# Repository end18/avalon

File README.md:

Avalon Gen3 Hasher
------------------

This project contains a circuit board, firmware and cgminer/bfgminer patch to get the new Avalon Gen3 ASICs (A3233Q48) hashing.

**Board features:**

  - Very efficient (~90%) DC/DC converter to power the ASICs
  - Adjustable voltage (0.75 - 1.25 V) to choose between efficiency and overclocking
  - USB-Interface to connect to a host running cgminer or bfgminer
  - TWI interface to chain multiple boards together
  - 100% flat surface on the bottom side to mount a usual heatsink
  - On-board temperature management
  - Fan connector with rotation speed measurement and PWM-control
  - Indicator LED to report USB-activity
  - 4-layer PCB for optimal heat/current transportation

**cgminer/bfgminer patch features:**

  - Reporting temperature, real ASIC frequency and fan-speed back to the host
  - Control of ASIC frequency in a big range from 62.5 to 5000 MHz in smallest possible steps
  - Control of a desired temperature

**Get support:**

* [Forum thread]
* - Will be updated soon.

**Get a board:**

Someone is selling some boards in the [Forum thread] soon.

  [Forum thread]: comming soon.

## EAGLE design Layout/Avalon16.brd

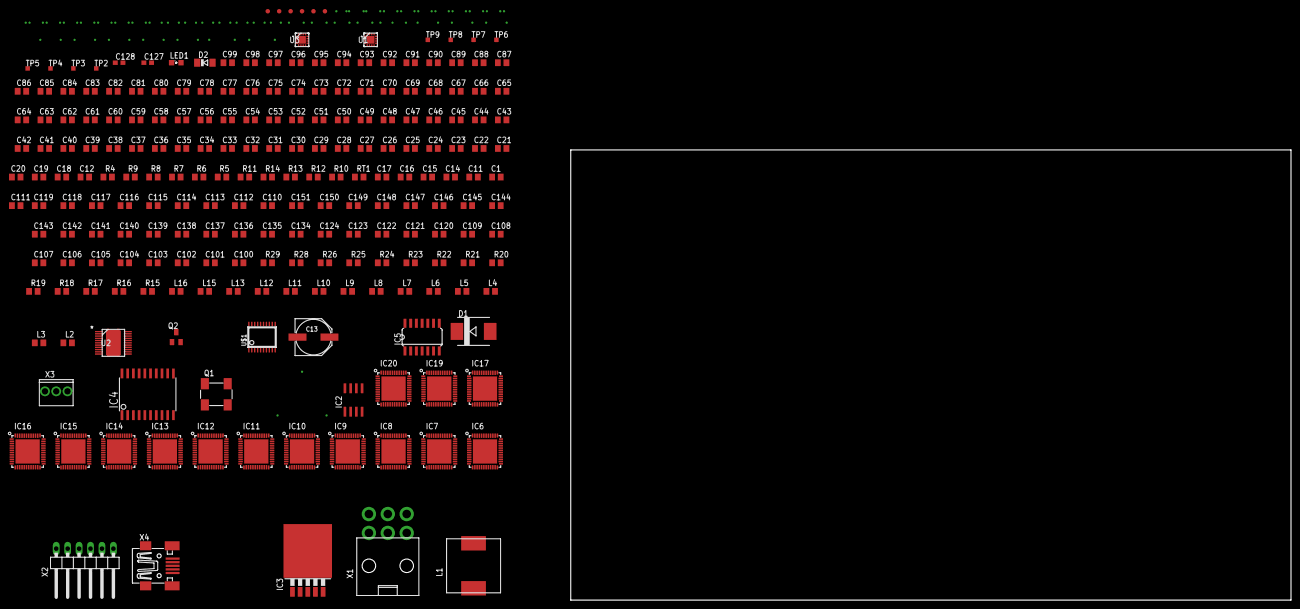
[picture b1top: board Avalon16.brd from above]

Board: 2 copper layers, 160.0 x 100.0 mm, 264 parts (0 on the bottom side), 115 nets, no tracks yet.

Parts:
C1, C11, C14, C15, C16: 100n; C0805
C12, C18, C19, C20, C21, C22, C23, C24, C25, C26, C27, C28, C29, C30, C31, C32, C33, C34, C35, C36, C37, C38, C39, C40, C41, C42, C43, C44, C45, C46, C47, C48, C49, C50, C51, C52, C53, C54, C55, C56, C57, C58, C59, C60, C61, C62, C63, C64, C65, C66, C67, C68, C69, C70, C71, C72, C73, C74, C75, C76, C77, C78, C79, C80, C81, C82, C83, C84, C85, C86, C87, C88, C89, C90, C91, C92, C93, C94, C95, C96, C97, C98, C99, C100, C101, C102, C103, C104, C105, C106, C107, C108, C109, C110, C111, C112, C113, C114, C115, C116, C117, C118, C119, C120, C121, C122, C123, C124, C134, C135, C136, C137, C138, C139, C140, C141, C142, C143, C144, C145, C146, C147, C148, C149, C150, C151: 1µ; C0805
C13: 1000µ/6.3V/EEEFP0J102AP; PANASONIC_F
C17: 470p; C0805
C127, C128: 0.1µ; C0603
CAC_1: 1nF; 0603
CBST_1: 100nF; 0603
CINX_1, CINX_2: 100nF; 0603
CIN_1, CIN_6: 10uF; 0805
CIN_2, CIN_3, CIN_4, CIN_5: 22uF; 1812
COUT_1, COUT_6: 22uF; 0805
COUT_2, COUT_3, COUT_4, COUT_5: 100uF; 1812
CREG_1: 1uF; 1206
CR_1: 22nF; 0603
CSNUB_1: 2.2nF; 0603
CSS_1: 120pF; 0201
CSS_2: 220pF; 0201
CVDD_1: 4.7uF; 0805
D1: MBRS340T3G; SMC
D2: 4448; SOD80C
FID1, FID2, FID3, FID4, FID5, FID6: 1mm; FIDUCIAL
GND93: WB_GND
IC2: NB3L553DG; SO8
IC3: LM2576S-3.3; TO263-5
IC4: PIC16LF1459; SOIC20
IC5: 74HC02D; SO14
IC6, IC7, IC8, IC9, IC10, IC11, IC12, IC13, IC14, IC15, IC16, IC17, IC19, IC20: A3255Q48; QFN48
L1: 100µ / Würth 7447709101; WUERTH-7447709101
L2, L3, L4, L5, L6, L7, L8, L9, L10, L11, L12, L13, L15, L16: 100µ; L0805
L14, L18: 2.2uH; SRN8040
L17: 500nH; SER2009
LED1: green; SML0805
Q1: 7W-25-000MBB-T; 7W
Q2: IRFML8244TRPBF; SOT23
R4, R10, R11, R13: 10k; R0805
R5, R6: 390; R0805
R7, R8, R9, R12: 100; R0805
R14: 1k; R0805
R15, R16, R17, R18, R19, R20, R21, R22, R23, R24, R25, R26, R28, R29: 100k; R0805
RBST_1: 2.05; 0402
RENABLE_1: 1k; 0402
RENB_1: 100k; 0402
RENT_1: 200k; 0402
RFB1: 200k; 0402
RFB2: 24.9k; 0402
RFB3: 150k; 0402
RFB4: 187k; 0402
RFBB_1: 10k; 0402
RFBT_1: 2.49k; 0402
RPGOOD_1: 100k; 0402
RPG_1, RPG_2: 100k; 0402
RR_1: 66.5k; 0402
RSNUB_1: 3; 0402
RSS_1: 39k; 0603
RT1: 2k2; 0805
RTRIP_1: 180k; 0402
TP2, TP3, TP4, TP5, TP6, TP7, TP8, TP9: TPSQTP10SQ; TP10SQ
U1, U3: TPS62130RGTR; S-PVQFN-N16
U2: TPS53355DQPR; R-PSON-N22
U$1: GTL2003; TSSOP20
X1: Molex 45558-0003; MOLEX-45558-0003
X2: ISP; 1X06/270
X3: Molex 22-04-1031; MOLEX-22-04-1031
X4: Würth 65100516121 / TE 1734035-2; 32005-301

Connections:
1: CSS_1.2, U1.9
3: RFB1.2, RFB2.2, U1.5
4: L14.1, U1.1, U1.2, U1.3
6: RPG_1.2, U1.4
7: CAC_1.2, RFBB_1.1, RFBT_1.2, U2.1
10: CAC_1.1, CR_1.2, RR_1.1
11: CBST_1.2, RBST_1.1
13: CREG_1.1, RPGOOD_1.2, U2.18
14: CSNUB_1.1, RSNUB_1.2
15: RBST_1.2, U2.4
16: RENABLE_1.2, RENB_1.1, RENT_1.1
17: RENABLE_1.1, U2.2
18: RPGOOD_1.1, U2.3
19: RSS_1.1, U2.20
20: RTRIP_1.2, U2.21
24: CSS_2.2, U3.9
25: L18.1, U3.1, U3.2, U3.3
26: RFB3.2, RFB4.2, U3.5
27: RPG_2.2, U3.4
!MCLR: IC4.4, R7.1, X2.1
!RESET1: C26.2, IC6.44, R15.2
!RESET2: C27.2, IC7.44, R16.2
!RESET3: C36.2, IC8.44, R17.2
!RESET4: C45.2, IC9.44, R18.2
!RESET5: C54.2, IC10.44, R19.2
!RESET6: C63.2, IC11.44, R20.2
!RESET7: C72.2, IC12.44, R21.2
!RESET8: C81.2, IC13.44, R22.2
!RESET9: C90.2, IC14.44, R23.2
!RESET10: C99.2, IC15.44, R24.2
!RESET11: C12.2, IC16.44, R25.2
!RESET12: C116.2, IC17.44, R26.2
!RESET14: C134.2, IC19.44, R28.2
!RESET15: C143.2, IC20.44, R29.2
+0V9: COUT_1.1, IC8.7, IC9.7, IC10.7, IC12.7, IC13.7, IC14.7, IC15.7, IC16.7, IC17.7, IC19.7, IC20.7, L14.2, RFB2.1, RPG_1.1, U1.7, U1.14
+1V8: C127.2, COUT_6.1, IC6.24, IC6.37, IC7.24, IC7.37, IC8.24, IC8.37, IC9.24, IC9.37, IC10.24, IC10.37, IC11.24, IC11.37, IC12.24, IC12.37, IC13.24, IC13.37, IC14.24, IC14.37, IC15.24, IC15.37, IC16.24, IC16.37, IC17.24, IC17.37, IC19.24, IC19.37, IC20.24, IC20.37, L2.1, L3.1, L4.1, L5.1, L6.1, L7.1, L8.1, L9.1, L10.1, L11.1, L12.1, L13.1, L15.1, L16.1, L18.2, R15.1, R16.1, R17.1, R18.1, R19.1, R20.1, R21.1, R22.1, R23.1, R24.1, R25.1, R26.1, R28.1, R29.1, RFB4.1, RPG_2.1, U3.7, U3.14, U$1.2
+3V3: C1.2, C11.2, C13.+, C14.2, C15.2, C23.2, C24.2, C34.2, C35.2, C43.2, C44.2, C52.2, C53.2, C61.2, C62.2, C70.2, C71.2, C79.2, C80.2, C88.2, C89.2, C97.2, C98.2, C106.2, C107.2, C114.2, C115.2, C123.2, C124.2, C128.2, C141.2, C142.2, C150.2, C151.2, IC2.1, IC2.8, IC3.4, IC4.1, IC5.14, L1.2, Q1.4, R4.1, R5.1, R6.1, R10.1, R11.1, RT1.2, TP6.TP, U$1.19, U$1.20, X2.2
+12V: CINX_1.1, CINX_2.1, CIN_1.1, CIN_2.1, CIN_3.1, CIN_4.1, CIN_5.1, CIN_6.1, CVDD_1.1, D2.C, IC3.1, RENT_1.2, U1.10, U1.11, U1.12, U1.13, U2.12, U2.13, U2.14, U2.15, U2.16, U2.17, U2.19, U3.10, U3.11, U3.12, U3.13, X1.1, X1.2, X1.3, X3.2
CLK1: IC2.2, IC6.9, IC7.9, IC8.9, IC9.9, IC10.9, IC19.9, IC20.9
CLK2: IC2.3, IC11.9, IC12.9, IC13.9, IC14.9, IC15.9, IC16.9, IC17.9
CONFIG1_1V8_N: IC6.2, U$1.4
CONFIG1_1V8_P: IC6.1, U$1.3
CONFIG1_1_2_N: IC6.35, IC7.2
CONFIG1_1_2_P: IC6.36, IC7.1
CONFIG1_2_3_N: IC7.35, IC8.2
CONFIG1_2_3_P: IC7.36, IC8.1
CONFIG1_3_4_N: IC8.35, IC9.2
CONFIG1_3_4_P: IC8.36, IC9.1
CONFIG1_4_5_N: IC9.35, IC10.2
CONFIG1_4_5_P: IC9.36, IC10.1
CONFIG1_5_6_N: IC10.35, IC19.2
CONFIG1_5_6_P: IC10.36, IC19.1
CONFIG1_6_7_N: IC19.35, IC20.2
CONFIG1_6_7_P: IC19.36, IC20.1
CONFIG1_N: IC4.8, U$1.17
CONFIG1_P: IC4.9, U$1.18
CONFIG2_1V8_N: IC11.2, U$1.6
CONFIG2_1V8_P: IC11.1, U$1.5
CONFIG2_1_2_N: IC11.35, IC12.2
CONFIG2_1_2_P: IC11.36, IC12.1
CONFIG2_2_3_N: IC12.35, IC13.2
CONFIG2_2_3_P: IC12.36, IC13.1
CONFIG2_3_4_N: IC13.35, IC14.2
CONFIG2_3_4_P: IC13.36, IC14.1
CONFIG2_4_5_N: IC14.35, IC15.2
CONFIG2_4_5_P: IC14.36, IC15.1
CONFIG2_5_6_N: IC15.35, IC16.2
CONFIG2_5_6_P: IC15.36, IC16.1
CONFIG2_6_7_N: IC16.35, IC17.2
CONFIG2_6_7_P: IC16.36, IC17.1
CONFIG2_N: IC4.7, U$1.15
CONFIG2_P: IC4.6, U$1.16
DVDD: C18.2, C19.2, C20.2, C21.2, C22.2, C29.2, C30.2, C31.2, C32.2, C33.2, C38.2, C39.2, C40.2, C41.2, C42.2, C47.2, C48.2, C49.2, C50.2, C51.2, C56.2, C57.2, C58.2, C59.2, C60.2, C65.2, C66.2, C67.2, C68.2, C69.2, C74.2, C75.2, C76.2, C77.2, C78.2, C83.2, C84.2, C85.2, C86.2, C87.2, C92.2, C93.2, C94.2, C95.2, C96.2, C101.2, C102.2, C103.2, C104.2, C105.2, C109.2, C110.2, C111.2, C112.2, C113.2, C118.2, C119.2, C120.2, C121.2, C122.2, C136.2, C137.2, C138.2, C139.2, C140.2, C145.2, C146.2, C147.2, C148.2, C149.2, CBST_1.1, COUT_2.1, COUT_3.1, COUT_4.1, COUT_5.1, CR_1.1, CSNUB_1.2, IC6.3, IC6.4, IC6.10, IC6.11, IC6.13, IC6.14, IC6.15, IC6.18, IC6.19, IC6.20, IC6.21, IC6.22, IC6.25, IC6.26, IC6.28, IC6.29, IC6.30, IC6.31, IC6.32, IC6.33, IC6.34, IC6.39, IC6.40, IC6.41, IC6.42, IC6.45, IC6.46, IC6.47, IC6.48, IC7.3, IC7.4, IC7.10, IC7.11, IC7.13, IC7.14, IC7.15, IC7.18, IC7.19, IC7.20, IC7.21, IC7.22, IC7.25, IC7.26, IC7.28, IC7.29, IC7.30, IC7.31, IC7.32, IC7.33, IC7.34, IC7.39, IC7.40, IC7.41, IC7.42, IC7.45, IC7.46, IC7.47, IC7.48, IC8.3, IC8.4, IC8.10, IC8.11, IC8.13, IC8.14, IC8.15, IC8.18, IC8.19, IC8.20, IC8.21, IC8.22, IC8.25, IC8.26, IC8.28, IC8.29, IC8.30, IC8.31, IC8.32, IC8.33, IC8.34, IC8.39, IC8.40, IC8.41, IC8.42, IC8.45, IC8.46, IC8.47, IC8.48, IC9.3, IC9.4, IC9.10, IC9.11, IC9.13, IC9.14, IC9.15, IC9.18, IC9.19, IC9.20, IC9.21, IC9.22, IC9.25, IC9.26, IC9.28, IC9.29, IC9.30, IC9.31, IC9.32, IC9.33, IC9.34, IC9.39, IC9.40, IC9.41, IC9.42, IC9.45, IC9.46, IC9.47, IC9.48, IC10.3, IC10.4, IC10.10, IC10.11, IC10.13, IC10.14, IC10.15, IC10.18, IC10.19, IC10.20, IC10.21, IC10.22, IC10.25, IC10.26, IC10.28, IC10.29, IC10.30, IC10.31, IC10.32, IC10.33, IC10.34, IC10.39, IC10.40, IC10.41, IC10.42, IC10.45, IC10.46, IC10.47, IC10.48, IC11.3, IC11.4, IC11.10, IC11.11, IC11.13, IC11.14, IC11.15, IC11.18, IC11.19, IC11.20, IC11.21, IC11.22, IC11.25, IC11.26, IC11.28, IC11.29, IC11.30, IC11.31, IC11.32, IC11.33, IC11.34, IC11.39, IC11.40, IC11.41, IC11.42, IC11.45, IC11.46, IC11.47, IC11.48, IC12.3, IC12.4, IC12.10, IC12.11, IC12.13, IC12.14, IC12.15, IC12.18, IC12.19, IC12.20, IC12.21, IC12.22, IC12.25, IC12.26, IC12.28, IC12.29, IC12.30, IC12.31, IC12.32, IC12.33, IC12.34, IC12.39, IC12.40, IC12.41, IC12.42, IC12.45, IC12.46, IC12.47, IC12.48, IC13.3, IC13.4, IC13.10, IC13.11, IC13.13, IC13.14, IC13.15, IC13.18, IC13.19, IC13.20, IC13.21, IC13.22, IC13.25, IC13.26, IC13.28, IC13.29, IC13.30, IC13.31, IC13.32, IC13.33, IC13.34, IC13.39, IC13.40, IC13.41, IC13.42, IC13.45, IC13.46, IC13.47, IC13.48, IC14.3, IC14.4, IC14.10, IC14.11, IC14.13, IC14.14, IC14.15, IC14.18, IC14.19, IC14.20, IC14.21, IC14.22, IC14.25, IC14.26, IC14.28, IC14.29, IC14.30, IC14.31, IC14.32, IC14.33, IC14.34, IC14.39, IC14.40, IC14.41, IC14.42, IC14.45, IC14.46, IC14.47, IC14.48, IC15.3, IC15.4, IC15.10, IC15.11, IC15.13, IC15.14, IC15.15, IC15.18, IC15.19, IC15.20, IC15.21, IC15.22, IC15.25, IC15.26, IC15.28, IC15.29, IC15.30, IC15.31, IC15.32, IC15.33, IC15.34, IC15.39, IC15.40, IC15.41, IC15.42, IC15.45, IC15.46, IC15.47, IC15.48, IC16.3, IC16.4, IC16.10, IC16.11, IC16.13, IC16.14, IC16.15, IC16.18, IC16.19, IC16.20, IC16.21, IC16.22, IC16.25, IC16.26, IC16.28, IC16.29, IC16.30, IC16.31, IC16.32, IC16.33, IC16.34, IC16.39, IC16.40, IC16.41, IC16.42, IC16.45, IC16.46, IC16.47, IC16.48, IC17.3, IC17.4, IC17.10, IC17.11, IC17.13, IC17.14, IC17.15, IC17.18, IC17.19, IC17.20, IC17.21, IC17.22, IC17.25, IC17.26, IC17.28, IC17.29, IC17.30, IC17.31, IC17.32, IC17.33, IC17.34, IC17.39, IC17.40, IC17.41, IC17.42, IC17.45, IC17.46, IC17.47, IC17.48, IC19.3, IC19.4, IC19.10, IC19.11, IC19.13, IC19.14, IC19.15, IC19.18, IC19.19, IC19.20, IC19.21, IC19.22, IC19.25, IC19.26, IC19.28, IC19.29, IC19.30, IC19.31, IC19.32, IC19.33, IC19.34, IC19.39, IC19.40, IC19.41, IC19.42, IC19.45, IC19.46, IC19.47, IC19.48, IC20.3, IC20.4, IC20.10, IC20.11, IC20.13, IC20.14, IC20.15, IC20.18, IC20.19, IC20.20, IC20.21, IC20.22, IC20.25, IC20.26, IC20.28, IC20.29, IC20.30, IC20.31, IC20.32, IC20.33, IC20.34, IC20.39, IC20.40, IC20.41, IC20.42, IC20.45, IC20.46, IC20.47, IC20.48, L17.1, L17.2, RFBT_1.1, RR_1.2, U2.6, U2.7, U2.8, U2.9, U2.10, U2.11
FAN_PWM: IC4.5, R12.1
GND: C1.1, C11.1, C12.1, C13.-, C14.1, C15.1, C16.1, C17.1, C18.1, C19.1, C20.1, C21.1, C22.1, C23.1, C24.1, C25.2, C26.1, C27.1, C28.2, C29.1, C30.1, C31.1, C32.1, C33.1, C34.1, C35.1, C36.1, C37.2, C38.1, C39.1, C40.1, C41.1, C42.1, C43.1, C44.1, C45.1, C46.2, C47.1, C48.1, C49.1, C50.1, C51.1, C52.1, C53.1, C54.1, C55.2, C56.1, C57.1, C58.1, C59.1, C60.1, C61.1, C62.1, C63.1, C64.2, C65.1, C66.1, C67.1, C68.1, C69.1, C70.1, C71.1, C72.1, C73.2, C74.1, C75.1, C76.1, C77.1, C78.1, C79.1, C80.1, C81.1, C82.2, C83.1, C84.1, C85.1, C86.1, C87.1, C88.1, C89.1, C90.1, C91.2, C92.1, C93.1, C94.1, C95.1, C96.1, C97.1, C98.1, C99.1, C100.2, C101.1, C102.1, C103.1, C104.1, C105.1, C106.1, C107.1, C108.2, C109.1, C110.1, C111.1, C112.1, C113.1, C114.1, C115.1, C116.1, C117.2, C118.1, C119.1, C120.1, C121.1, C122.1, C123.1, C124.1, C127.1, C128.1, C134.1, C135.2, C136.1, C137.1, C138.1, C139.1, C140.1, C141.1, C142.1, C143.1, C144.2, C145.1, C146.1, C147.1, C148.1, C149.1, C150.1, C151.1, CINX_1.2, CINX_2.2, CIN_1.2, CIN_2.2, CIN_3.2, CIN_4.2, CIN_5.2, CIN_6.2, COUT_1.2, COUT_2.2, COUT_3.2, COUT_4.2, COUT_5.2, COUT_6.2, CREG_1.2, CSS_1.1, CSS_2.1, CVDD_1.2, D1.A, GND93.1, IC2.4, IC3.3, IC3.5, IC3.6, IC4.20, IC5.7, IC6.5, IC6.8, IC6.12, IC6.23, IC6.27, IC6.38, IC6.EXP, IC7.5, IC7.8, IC7.12, IC7.23, IC7.27, IC7.38, IC7.EXP, IC8.5, IC8.8, IC8.12, IC8.23, IC8.27, IC8.38, IC8.EXP, IC9.5, IC9.8, IC9.12, IC9.23, IC9.27, IC9.38, IC9.EXP, IC10.5, IC10.8, IC10.12, IC10.23, IC10.27, IC10.38, IC10.EXP, IC11.5, IC11.8, IC11.12, IC11.23, IC11.27, IC11.38, IC11.EXP, IC12.5, IC12.8, IC12.12, IC12.23, IC12.27, IC12.38, IC12.EXP, IC13.5, IC13.8, IC13.12, IC13.23, IC13.27, IC13.38, IC13.EXP, IC14.5, IC14.8, IC14.12, IC14.23, IC14.27, IC14.38, IC14.EXP, IC15.5, IC15.8, IC15.12, IC15.23, IC15.27, IC15.38, IC15.EXP, IC16.5, IC16.8, IC16.12, IC16.23, IC16.27, IC16.38, IC16.EXP, IC17.5, IC17.8, IC17.12, IC17.23, IC17.27, IC17.38, IC17.EXP, IC19.5, IC19.8, IC19.12, IC19.23, IC19.27, IC19.38, IC19.EXP, IC20.5, IC20.8, IC20.12, IC20.23, IC20.27, IC20.38, IC20.EXP, LED1.C, Q1.2, Q2.2, R13.2, R14.2, RENB_1.2, RFB1.1, RFB3.1, RFBB_1.2, RSNUB_1.1, RSS_1.2, RTRIP_1.1, TP9.TP, U1.6, U1.8, U1.15, U1.16, U1.17, U2.23, U3.6, U3.8, U3.15, U3.16, U3.17, U$1.1, X1.4, X1.5, X1.6, X2.3, X4.5, X4.M1, X4.M2, X4.M3, X4.M4
ICSPCLK: IC4.15, X2.5
ICSPDAT: IC4.16, X2.4
LED: IC4.2, R9.2
unnamed: IC20.36, TP2.TP
unnamed: C16.2, IC4.17
unnamed: D1.C, IC3.2, L1.1
unnamed: IC2.5, Q1.3
unnamed: D2.A, Q2.3, X3.1
unnamed: IC5.5, IC5.13, R8.1
unnamed: IC5.2, IC5.3, IC5.4
unnamed: Q2.1, R12.2, R13.1
unnamed: C17.2, IC5.6, R8.2
unnamed: R4.2, R7.2, X3.3
unnamed: LED1.A, R9.1
NTC: IC4.14, R14.1, RT1.1
OSC_EN: IC4.3, Q1.1
REPORT_1V8_N: IC6.16, IC7.16, IC8.16, IC9.16, IC10.16, IC11.16, IC12.16, IC13.16, IC14.16, IC15.16, IC16.16, IC17.16, IC19.16, IC20.16, U$1.8
REPORT_1V8_P: IC6.17, IC7.17, IC8.17, IC9.17, IC10.17, IC11.17, IC12.17, IC13.17, IC14.17, IC15.17, IC16.17, IC17.17, IC19.17, IC20.17, U$1.7
REPORT_CLK: IC4.10, IC5.1
REPORT_DATA: IC4.12, IC5.10
REPORT_N: IC5.8, IC5.9, IC5.12, R6.2, U$1.13
REPORT_P: IC5.11, R5.2, U$1.14
SCL: IC4.11, R11.2, TP7.TP
SDA: IC4.13, R10.2, TP8.TP
USB_DM: IC4.18, X4.2
USB_DP: IC4.19, X4.3
VDD_PLL1: C25.1, IC6.6, L2.2
VDD_PLL2: C28.1, IC7.6, L3.2
VDD_PLL3: C37.1, IC8.6, L4.2
VDD_PLL4: C46.1, IC9.6, L5.2
VDD_PLL5: C55.1, IC10.6, L6.2
VDD_PLL6: C64.1, IC11.6, L7.2
VDD_PLL7: C73.1, IC12.6, L8.2
VDD_PLL8: C82.1, IC13.6, L9.2
VDD_PLL9: C91.1, IC14.6, L10.2
VDD_PLL10: C100.1, IC15.6, L11.2
VDD_PLL11: C108.1, IC16.6, L12.2
VDD_PLL12: C117.1, IC17.6, L13.2
VDD_PLL14: C135.1, IC19.6, L15.2
VDD_PLL15: C144.1, IC20.6, L16.2

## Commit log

2014-03-19 Add for Avalon Gen 3
    add for A3233, GTL2003, LXDC3EP
2014-03-20 add level translator
2014-03-22 change power units
